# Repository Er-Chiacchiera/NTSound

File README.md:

# NTSound
Progetto con innova lazio

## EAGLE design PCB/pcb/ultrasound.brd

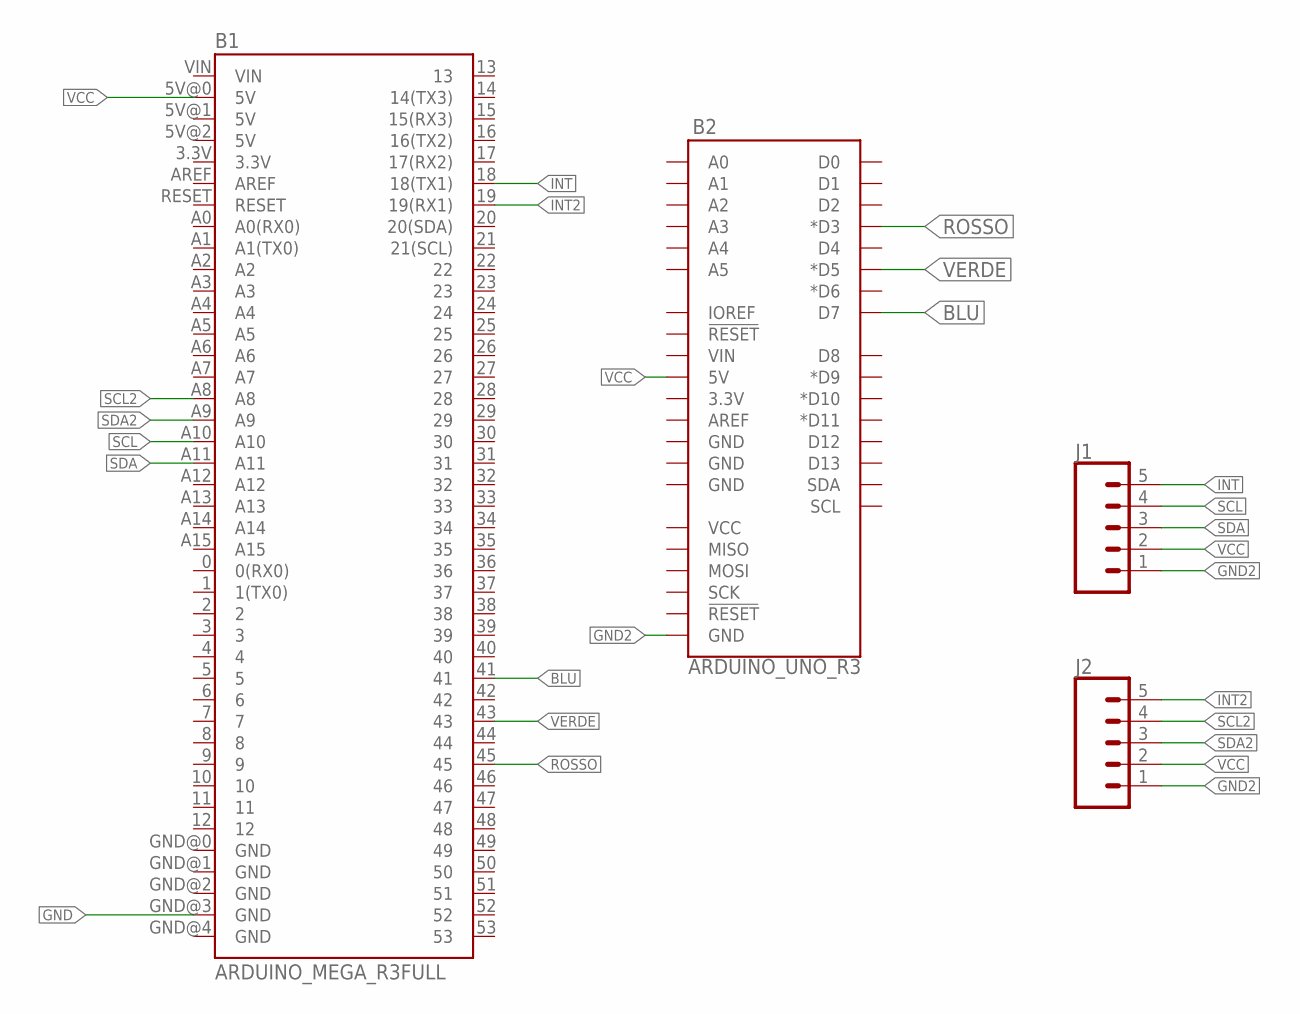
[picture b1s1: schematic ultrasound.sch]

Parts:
B1: ARDUINO_MEGA_R3FULL; ARDUINO_MEGA
B2: ARDUINO_UNO_R3; ARDUINO_R3
J1, J2: CONN_05; 1X05

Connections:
BLU: B1.41, B2.D7
GND: B1.GND@3 (GND)
GND2: B2.GND@1 (GND), J1.1, J2.1
INT: B1.18 (18(TX1)), J1.5
INT2: B1.19 (19(RX1)), J2.5
ROSSO: B1.45, B2.D3 (*D3)
SCL: B1.A10, J1.4
SCL2: B1.A8, J2.4
SDA: B1.A11, J1.3
SDA2: B1.A9, J2.3
VCC: B1.5V@0 (5V), B2.5V, J1.2, J2.2
VERDE: B1.43, B2.D5 (*D5)

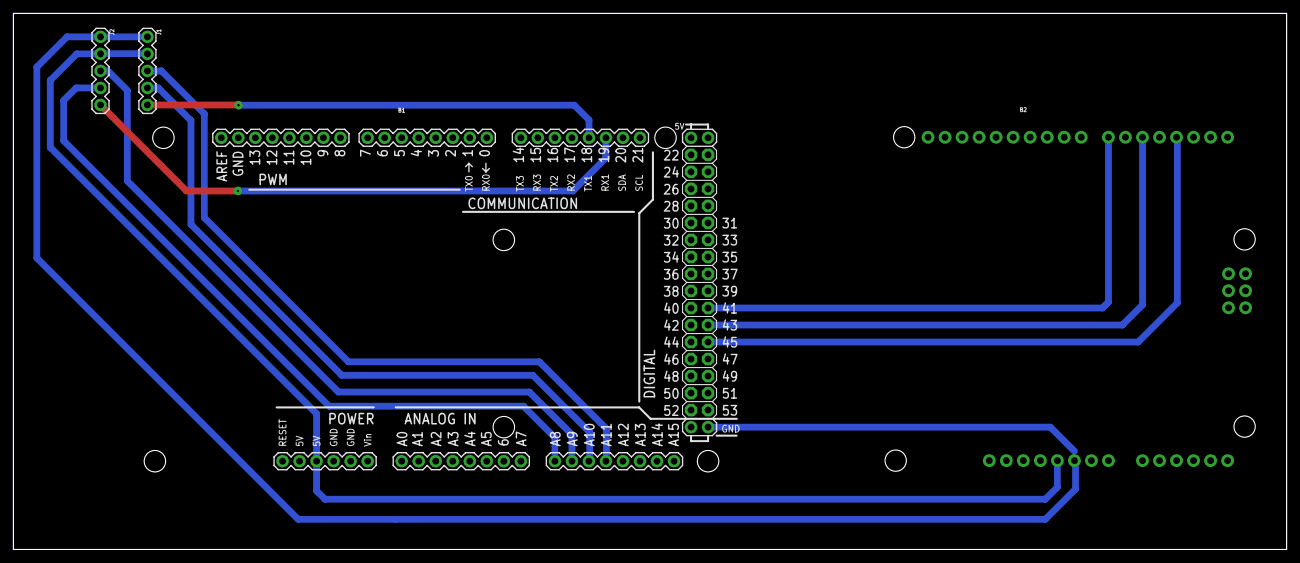
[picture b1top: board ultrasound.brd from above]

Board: 2 copper layers, 190.0 x 80.0 mm, 4 parts (0 on the bottom side), 11 nets.

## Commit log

2018-05-10 file
2018-05-10 prova
2018-05-10 programmi prova
2018-05-14 Dimesioni PCB
2018-05-14 eagle
2018-05-14 finale
2018-05-15 pcb finale
2018-05-15 elimino programma sensore
2018-05-15 musica ahaha
2018-05-15 Auto stash before merge of "master" and "origin/master"
2018-05-15 pulizia
2018-05-15 Lista casse
2018-05-15 Sistemazione file
2018-05-15 Componenti
2018-05-16 problema risolto
2018-05-16 pcb inserita
2018-05-16 Aggiornamento preventivo (non completo)
2018-05-16 lista(non completa)
2018-05-17 risoluzione problema
2018-05-17 immagini mani
2018-05-17 Aggiunta programma e libreria per sensore gesti
2018-05-17 Pitch
2018-05-20 pin nuovi
2018-05-25 Business plan guida
2018-10-04 vecchie e nuove canzoni
2018-10-04 photo e datasheet sensor
2018-10-04 git ignore
2018-10-12 canzoni Makerfaire
2018-10-12 backup

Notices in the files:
parts and their libraries:
SparkFun-Boards: Licensing: Creative Commons ShareAlike 4.0 International - https://creativecommons.org/licenses/by-sa/4.0
